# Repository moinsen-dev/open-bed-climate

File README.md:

# Open Bed Climate

**An open-source, local-first bed climate system you can build, repair and adapt yourself.**

Open Bed Climate cools and warms each side of your bed with water, tracks presence, heart rate and breathing,
and runs your sleep temperature schedule — like the commercial "smart mattress cover" systems, but:

- 🔓 **Open:** hardware (CERN-OHL-S-2.0) and software (Apache-2.0), designed clean-room from public information
- 🏠 **Local-first:** no cloud, no account, no subscription; native **Home Assistant** integration
- 🔧 **Standard parts:** PC-watercooling components, Peltier modules, Raspberry Pi Pico, ESP32, certified plug-in power supplies
- 🧩 **DIY kits you can adapt:** one zone or two, cheap or high-performance, three sensing options

> ⚠️ **Safety first.** This project combines water, several hundred watts and a sleeping person.
> Read [SAFETY.md](SAFETY.md) before you build anything. Nothing here is certified.

## Status: design phase. Help us build the first prototype!

| Area | State |
|---|---|
| Feature parity analysis | ✅ [docs/FEATURES.md](docs/FEATURES.md) |
| System design, safety concept | ✅ [docs/design/](docs/design/) · [SAFETY.md](SAFETY.md) |
| Kits and parts catalog | ✅ first version: [hardware/](hardware/) |
| Reference software (thermal model, control + safety logic, protocol, schedules) | ✅ tested: [software/obc](software/obc) |
| Control firmware for the Pico 2 (Rust/embassy) | ✅ compiles, matches the reference; 🔜 first hardware bring-up: [firmware/](firmware/) |
| Hub: ESPHome component + Home Assistant entities, night programs on the hub | ✅ compiles for ESP32-S3, protocol and schedule host-tested; 🔜 first hardware run: [hub/esphome/](hub/esphome/) |
| First physical build + measurements | 🔜 **help wanted, the most valuable contribution right now**: follow the [build guide](docs/build/) |

## Pick a kit

| Kit | Zones | Best for | Approx. coldest water* |
|---|---|---|---|
| [Solo Starter](hardware/kits/solo-starter.toml) | 1 | first build, single sleeper, lowest cost | ~21.7 °C |
| [Duo Standard](hardware/kits/duo-standard.toml) | 2 | couples, strongest cooling from standard parts | ~18.8 °C |
| [Duo Reference](hardware/kits/duo-reference.toml) | 2 | experienced builders, custom PCBs, best biometrics | ~18.5 °C |

\* Model estimate, sleeper in bed in a 25 °C room. All kits warm to 43 °C. Kits are plain TOML files: copy one,
change it, and the test suite checks whether your build can deliver what it claims.

## How it works

```
 bed:   [ water mat ] ←─ water lines ─→ ┌──────────────── hub ────────────────┐
        [ sensing   ] ── data cable ──→ │ Peltier thermal module(s), pump      │
                                        │ Pico 2 control MCU (safety limits)   │
                                        │ ESP32/ESPHome hub ⇄ Home Assistant   │
                                        │ certified 24 V + 12 V supplies       │
                                        └──────────────────────────────────────┘
```

Details: [architecture](docs/design/00-architecture.md) · [thermal](docs/design/01-thermal-fluidics.md) ·
[electrical safety](docs/design/02-electrical-safety.md) · [sensing](docs/design/03-sensing-biometrics.md) ·
[protocol](docs/design/04-firmware-protocol.md) · [software](docs/design/05-bed-software.md) ·
[open decisions](docs/design/OPEN-DECISIONS.md)

## Get involved

Builders, parts hunters, electronics and textile people, firmware and Home Assistant developers, writers:
there is a place for you. Start with [CONTRIBUTING.md](CONTRIBUTING.md).

**Build it:** the [build guide for prototype 0](docs/build/) (Solo Starter, bench first, then bed) takes you
step by step from parts to a commissioned unit and the measurements the model still needs.

```sh
cd software/obc && uv run pytest -q    # reference model, safety logic, kit checks
cd firmware && cargo test               # firmware core vs. golden vectors
```

## Background

Commercial systems in this space (e.g. Eight Sleep Pod) are cloud-bound and subscription-based. A community has
already built local replacements for older Pod hardware; see [docs/research/prior-art.md](docs/research/prior-art.md).
Open Bed Climate takes a different route: **our own open hardware**, so nobody depends on a vendor's servers to sleep well.
Open Bed Climate is not affiliated with or endorsed by Eight Sleep.

## License
Software and documentation: [Apache-2.0](LICENSE) · Hardware designs: [CERN-OHL-S-2.0](LICENSE-HARDWARE)

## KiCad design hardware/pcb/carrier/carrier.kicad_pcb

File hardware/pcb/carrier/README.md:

# Tier 0 carrier PCB, Rev A

> ⚠️ **Rev A is UNTESTED: review it before you order.** Nobody has built or measured it yet. Read
> [SAFETY.md](../../../SAFETY.md) first. Please post a build report if you build one.

The carrier replaces the perfboard and loose breakout boards of [step 2](../../../docs/build/02-control-board.md)
with one 100 × 100 mm, 2-layer board, so a small series (~10 units) can be ordered assembled. It carries **signals
and the 12 V aux rail only**. The TEC high-current path stays off-board, wired with ≥ 2.5 mm²:
24 V brick → DPS5020 → 20 A fuse → zone relay → polarity relays → TECs
([step 3](../../../docs/build/03-power-path.md)).

What plugs in:
- Raspberry Pi Pico 2 on 2 × 1x20 female headers
- ESP32-S3-DevKitC-1 on 2 × 1x22 female headers
- Screw terminals for every external wire: 5.08 mm for 12 V loads and power, 3.5 mm for sensors

Licence: CERN-OHL-S-2.0, like the rest of the hardware.

## Block diagram

```mermaid
flowchart LR
  IN["12 V aux brick<br/>barrel jack (Solo, <= 5 A) or 12V IN screw terminal"] --> F["mini blade fuse<br/>5 A (7.5 A on 2 oz)"] --> TVS["SMBJ15A TVS"] --> RP["P-FET reverse-polarity<br/>(AOD4185)"] --> V12(("+12V"))
  V12 --> BUCK["LM2596S-5.0<br/>12 -> 5 V, 3 A"] --> V5(("+5V"))
  V5 -- "SS34" --> PICO["Pico 2 (VSYS)"]
  V5 -- "SS34" --> ESP["ESP32-S3-DevKitC-1 (5V)"]
  PICO -- "3V3 OUT" --> V33(("+3V3"))
  PICO <-- "OPL UART GP0/GP1 460800 Bd" --> ESP
  ESP --- I2CH["I2C HUB header<br/>(room SHT45)"]
  PICO -- "I2C0 GP8/GP9" --> ADS["ADS1115 @0x48"] --- NTC["4x NTC divider<br/>10k 0.1 % + RC"]
  PICO -- "UART1 GP4/GP5, DE GP6" --> RS["SP3485"] --> DPS["RS-485 A/B/GND<br/>to the DPS module(s)"]
  PICO -- "GP10..13 / GP16..19" --> DRV["8x AO3400A low-side<br/>220R gate, 4.7k pull-down, SS34 flyback"]
  V12 --> LOOP["CUTOFF LOOP terminal<br/>(bimetal cutoffs in series)"] --> COIL["zone relay coil"] --> DRV
  V12 --> LOADS["polarity coils A/B, pump, fan"] --> DRV
  FLOW["flow GP14/GP20"] & LEAK["leak GP21"] & LEVEL["level GP22"] -- "1k + BAT54S clamp + 10k pull-up" --> PICO
```

## Terminals and pins (cross-referenced to `board.rs`)

The pin map comes from [`firmware/obc-pico2/src/board.rs`](../../../firmware/obc-pico2/src/board.rs).
[`software/obc/tests/test_carrier_pcb.py`](../../../software/obc/tests/test_carrier_pcb.py) parses
`carrier.kicad_pcb` and checks it against `board.rs` and
[`hub/esphome/obc-hub-common.yaml`](../../../hub/esphome/obc-hub-common.yaml) in CI. Pin 1 is the square pad.
Zone 0's terminals run along the top edge, zone 1's along the bottom edge (mirrored). Silk labels sit next to each
block, with the pin names written in left-to-right order.

| Terminal (zone 0 / zone 1) | Pins | Function | Pico 2 (`board.rs`) |
|---|---|---|---|
| J13 / J20 `CUTOFF LOOP` | 1 `12V` out, 2 `RET` | +12 V out to the bimetal cutoffs in series (all 50 °C and 80 °C) and back. **The return is the only feed of the zone relay coil.** | none, pure hardware |
| J14 / J21 `ZONE RLY` | 1 `+` coil (from RET), 2 `−` driver | zone (enable) relay coil, flyback across the coil | GP10 / GP16 |
| J15 + J16 / J22 + J23 `POL A`, `POL B` | 1 `+` 12 V, 2 `−` driver | polarity relay coils: 2 × SPDT (shopping list) on A and B, both switched by one MOSFET, each with its own flyback. **One DPDT relay: use POL A only.** | GP11 / GP17 (low = cool) |
| J17 / J24 `PUMP` | 1 `+` 12 V, 2 `−` | pump, ≥ 2 A, PWM-capable MOSFET | GP12 / GP18 |
| J18 / J25 `FAN` | 1 `+` 12 V, 2 `−` | heatsink fans, ≥ 2 A | GP13 / GP19 |
| J19 / J26 `FLOW` | 1 `5V`, 2 `G`, 3 `S` | hall flow sensor; 1 kΩ series, BAT54S clamp to 3.3 V/GND, 10 kΩ pull-up (5 V outputs are safe) | GP14 / GP20 |
| J4 / J6 `NTC WTR` | 1 `N` node, 2 `G` | water NTC: 3.3 V → 10 kΩ 0.1 % → node → NTC → GND, 1 kΩ/100 nF to the ADS | ADS1115 A0 / A2 |
| J5 / J7 `NTC HOT` | 1 `N`, 2 `G` | TEC hot-side NTC | ADS1115 A1 / A3 |

| Terminal (right edge) | Pins | Function | Pico 2 |
|---|---|---|---|
| J10 `RS-485` | 1 `A`, 2 `B`, 3 `G` | Modbus to the DPS module(s); JP1 `TERM` = 120 Ω across A/B (fit only if this end has no other termination) | UART1 GP4 (TX→DI) / GP5 (RO→RX), DE + /RE on GP6 (10 kΩ pull-down = receive) |
| J11 `LEAK` | 1 `12V`, 2 `G`, 3 `S` | leak module (powered from 12 V); contact to GND while dry. LOW = dry, open = fault | GP21 (10 kΩ pull-up) |
| J12 `LEVEL` | 1 `5V`, 2 `G`, 3 `S` | level sensor at 5 V; LOW = OK, open = fault. The clamp makes a 5 V output safe; the divider from the shopping list is not needed | GP22 (10 kΩ pull-up) |
| J2 `12V IN` | 1 `+12V`, 2 `GND` | 12 V aux brick (use this one for Duo) | |
| J1 barrel 5.5 × 2.5 | centre + | in parallel with J2. **Solo only, ≤ 5 A** | |
| J3 `STAR GND` | 1, 2 GND | **one** wire to the star point near the DPS (24 V −). Do not link 12 V − and 24 V − anywhere else | |

| Header | Pins | Notes |
|---|---|---|
| J9 `I2C HUB` | 1 ESP 3V3, 2 GND, 3 SDA = ESP32 GPIO8, 4 SCL = GPIO9 | room SHT45 for the dew-point guard. 4.7 kΩ pull-ups on board. The hub YAML only mentions the SHT45 in a comment; add `i2c: {sda: GPIO8, scl: GPIO9}` and an `sht4x` sensor, then set `room_temperature` / `room_humidity` |
| J8 `I2C PICO` | 1 3V3, 2 GND, 3 SDA = GP8, 4 SCL = GP9 | expansion on the ADS1115 bus (avoid address 0x48) |
| TP1–TP4 | 12V, 5V, 3V3, GND | test points (2 mm pads) |

All eight driver gates have a **4.7 kΩ pull-down** (RP2350-E9: ≤ 8.2 kΩ). An unflashed, crashed or reset Pico
leaves every output off, and the test checks every gate for it. Each zone relay coil gets +12 V **only** through its
CUTOFF LOOP terminal. An open cutoff or an unplugged loop drops the relay whatever the MCU does, and the test checks
that too. The flyback diode sits directly across the coil, so an opening bimetal never has to break the coil
current as an arc.

## Files

| Path | What |
|---|---|
| `scripts/design.py` | **source of truth**: every part with symbol, footprint, value, LCSC number and the net on each pin |
| `scripts/gen_lib.py` | project library: ESP32-S3-DevKitC-1 symbol, socket footprints for both modules |
| `scripts/gen_sch.py` | `carrier.kicad_sch`: one sheet, grouped by function, net labels on every pin, no-connect flags, power flags |
| `scripts/gen_pcb.py` | `carrier.kicad_pcb`: placement, nets, outline, silkscreen, net classes, JLC rules (`carrier.kicad_pro`) |
| `scripts/route.py` | Freerouting autoroute, GND pours on both layers, GND stitching vias |
| `scripts/silk.py` | post-route silkscreen pass: connector refs to F.Fab, test point / header / jumper labels, back-side labels for the NTC terminals hidden by the barrel jack |
| `scripts/fab.py` | ERC/DRC, Gerbers + drill, JLC BOM/CPL, full BOM, PDFs, renders into `fab/` |
| `build.sh` | runs all of the above |
| `fab/` | `carrier-rev-a-gerbers.zip`, `jlc-bom.csv`, `jlc-cpl.csv`, `bom-full.csv`, `carrier-schematic.pdf`, `carrier-assembly-top.pdf`, `carrier.net`, `reports/` (ERC, DRC), `renders/` |

Rebuild (KiCad 10, and Freerouting 1.9.0 on Java 17: `freerouting-1.9.0.jar` from
<https://github.com/freerouting/freerouting/releases/tag/v1.9.0>):

```sh
FREEROUTING_JAR=~/Downloads/freerouting-1.9.0.jar JAVA=/opt/homebrew/opt/openjdk@17/bin/java ./build.sh
```

Change the design in `scripts/design.py`, never in the generated KiCad files. Freerouting isn't deterministic, so a
rebuild gives different traces; re-run DRC and look at the renders.

## Board

- **100 × 100 mm, 2 layers**, 1.6 mm, M3 mounting holes (4, at the free spots, not the corners: the terminal rows
  run the full width). 126 footprints: 88 SMD parts for JLC assembly, the rest are THT/hand-soldered or holes.
- Track widths: signals 0.25 mm, loads (drains, coils, 5 V) 0.8 mm, 12 V 1.5 mm. GND pours on both layers, about
  200 vias including GND stitching. JLC-safe rules: clearance 0.2 mm (MSOP pads trimmed to TI's 0.30 mm land
  pattern), vias 0.6/0.3 mm, hole to hole ≥ 0.5 mm, copper to edge ≥ 0.3 mm. No copper under the ESP32 antenna.
- **Checks (Rev A as generated): ERC 0 violations. DRC 0 errors, 0 unconnected, schematic parity clean.**
  15 silkscreen-only warnings (small labels touching a pad or another label) are left; JLC clips silk on pads.
  Pin labels next to the terminals are 0.8 mm high: check they're legible in JLC's preview.
  Reports: `fab/reports/`.
- Renders: `fab/renders/render-top.png`, `render-bottom.png`, `render-3d.png`, `top-layers.svg`,
  `bottom-layers.svg`. The 12 × 12 mm inductor has no 3D model in KiCad's library and shows as a bare footprint.

## Ordering (JLCPCB)

1. **PCB**: upload `fab/carrier-rev-a-gerbers.zip`, 2 layers, 100 × 100 mm, 1.6 mm FR-4, HASL lead-free, 1 oz
   copper (5 A input). For Duo boards with all 12 V loads near their maximum, choose 2 oz outer copper (7.5 A, see
   limitations). Quantity 10.
2. **Assembly**: PCBA, Economic, top side, "Confirm parts placement". Upload `fab/jlc-bom.csv` and `fab/jlc-cpl.csv`.
3. In the BOM step, check every match. Parts **without an LCSC number** need one picked from JLC's library first:
   - AOD4185 (P-FET, TO-252, −40 V, ≤ 15 mΩ)
   - SS54 (5 A Schottky, SMC)
   - BZT52C12 (SOD-123)
   - 33 µH ≥ 4 A shielded 12 × 12 mm inductor
   - 100 µF 35 V and 220 µF 16 V electrolytics (6.3 × 7.7 mm, low ESR)
   - 10 kΩ **0.1 %** 0603 resistors (×4, NTC dividers: these set the temperature accuracy)

   The numbers marked "check" in `bom-full.csv` are the usual JLC basic parts but weren't confirmed on a product
   page while Rev A was drawn up.
4. In the placement preview, **check the rotation of every polarized part**: diodes, LED, electrolytics, SOT-23,
   ADS1115, SP3485, LM2596. KiCad and JLC rotation conventions differ for some packages; fix any wrong one in the
   preview.
5. **Hand-soldered THT parts** (not in the JLC files; buy them separately or add them as JLC THT assembly):

   | Qty | Part |
   |---|---|
   | 14 | screw terminal 5.08 mm, 2-pin (Phoenix MKDS 1,5/2-5.08 or compatible, e.g. KF128/DG128-2P) |
   | 4 | screw terminal 3.5 mm, 2-pin (NTC) |
   | 5 | screw terminal 3.5 mm, 3-pin (flow ×2, RS-485, leak, level) |
   | 2 + 2 | 1x20 and 1x22 female headers, 2.54 mm (Pico 2 / ESP32 sockets) |
   | 1 | DC barrel jack 5.5 × 2.5 mm, 3-pin THT, horizontal, with the pin layout of KiCad's `BarrelJack_Horizontal` (e.g. CUI PJ-063AH-class): **check the pins against the footprint**, a mismatched jack leaves GND or +12 V open |
   | 1 | Keystone 3568 mini blade fuse holder + ATM fuse: 5 A (1 oz board) or 7.5 A (2 oz board) |
   | 2 + 1 | 1x4 and 1x2 pin headers, jumper |
   | 4 | test points (2 mm pads): bare wire loops or nothing |

   Check each terminal block's footprint against your part. The Phoenix footprints assume the wire entry faces the
   board edge (verify on the 3D render before ordering).

### Cost estimate, 10 assembled boards (Oct 2026, rough)

| Item | ~USD for 10 |
|---|---|
| PCB 2 layers 100 × 100 mm, 1 oz | 5–10 (2 oz: +15) |
| PCBA setup + stencil | 10 |
| Extended-part fees (~10 unique extended parts × $3) | 30 |
| SMD components (ADS1115 ≈ $3 is the biggest item) | 60–80 |
| Placement and soldering | 5–10 |
| THT parts (≈25 terminals, sockets, jack, fuse holder) | 60–90 |
| Shipping to the EU + import VAT | 40–60 |
| **Total** | **≈ 210–290, i.e. ≈ €20–27 per board** |

That's without the Pico 2 and ESP32-S3-DevKitC-1 (about €6 + €15 each). Prices move: get a live quote.
AISLER (EU, PCB + assembly) or PCBWay take the same Gerbers. Their BOM formats differ: use `bom-full.csv` and
the KiCad position file `fab/reports/pos-kicad.csv`.

## Known limitations (Rev A)

- **Untested.** Not built, not powered, not measured. The first boards are a bring-up exercise: follow the
  [step 2 checkpoint](../../../docs/build/02-control-board.md) (gate pull-downs, reset test, rails) before you
  connect relays or TECs.
- **12 V current.** The 12 V traces are 1.5 mm (IPC-2221, external layer): about 4.5 A at +20 °C on 1 oz copper,
  about 7.5 A on 2 oz. Each zone's branch carries at most ~3.5 A (pump + fans + coils), but the input path carries
  the total. So: **1 oz board → 5 A fuse, ≤ 5 A total** (enough for Solo, ~3–4 A). **Duo near full load → order
  2 oz copper and fit a 7.5 A fuse.** Measure the real 12 V current at bring-up either way. The barrel jack is for
  ≤ 5 A only.
- **Reverse protection** drops ~0.1 V at 7 A (AOD4185, ~0.7 W). A 24 V brick plugged in by mistake makes the
  SMBJ15A TVS conduct and blows the fuse. It's a crowbar, so check the fuse after any wrong plug.
- **5 V back-feed.** The board's 5 V reaches the Pico and the ESP32 through Schottkys, so USB on either module
  never back-feeds into the board. Whether the DevKitC's own USB port can be back-fed from its 5V pin depends on
  the DevKitC revision. Prefer **not** to plug ESP32 USB in while the board is powered.
- **ESP32 row spacing** (22.86 mm) and pin order come from Espressif's DevKitC-1 v1.1 dimension drawing (DXF) and
  user guide. v1.0 boards have the same header. **Measure your module with calipers** before ordering. A clone with
  25.4 mm rows won't fit.
- **ESP32 antenna**: the antenna end has no copper on either layer, but the module still sits over the carrier's
  ground plane. Mount the carrier so the antenna isn't covered by metal.
- **Under-module parts**: low SMD parts sit between the socket rows of both modules. They are 8.5 mm below the
  module. Unplug the module to probe them.
- **Freerouting**: the traces are autorouted, not hand-optimised. Before ordering, look at the buck loop
  (LM2596 → SS54 → inductor → output cap) and the 12 V path in KiCad, and shorten them by hand if you can.
- **Pump/fan PWM**: since firmware 0.2 the MOSFETs switch the pump and fan supply at 25 kHz PWM. Use 2- or 3-pin
  fans; 4-wire PWM fans and the DDC's PWM input aren't broken out.
- **No on-board RS-485 bias resistors and no TVS on A/B.** The DPS-side adapter usually biases the bus. Keep the
  bus short and inside the enclosure.
- **LCSC numbers**: about half were confirmed on a product page (marked in `bom-full.csv`). The rest need checking
  in JLC's BOM matcher, and a few must be picked (see Ordering).

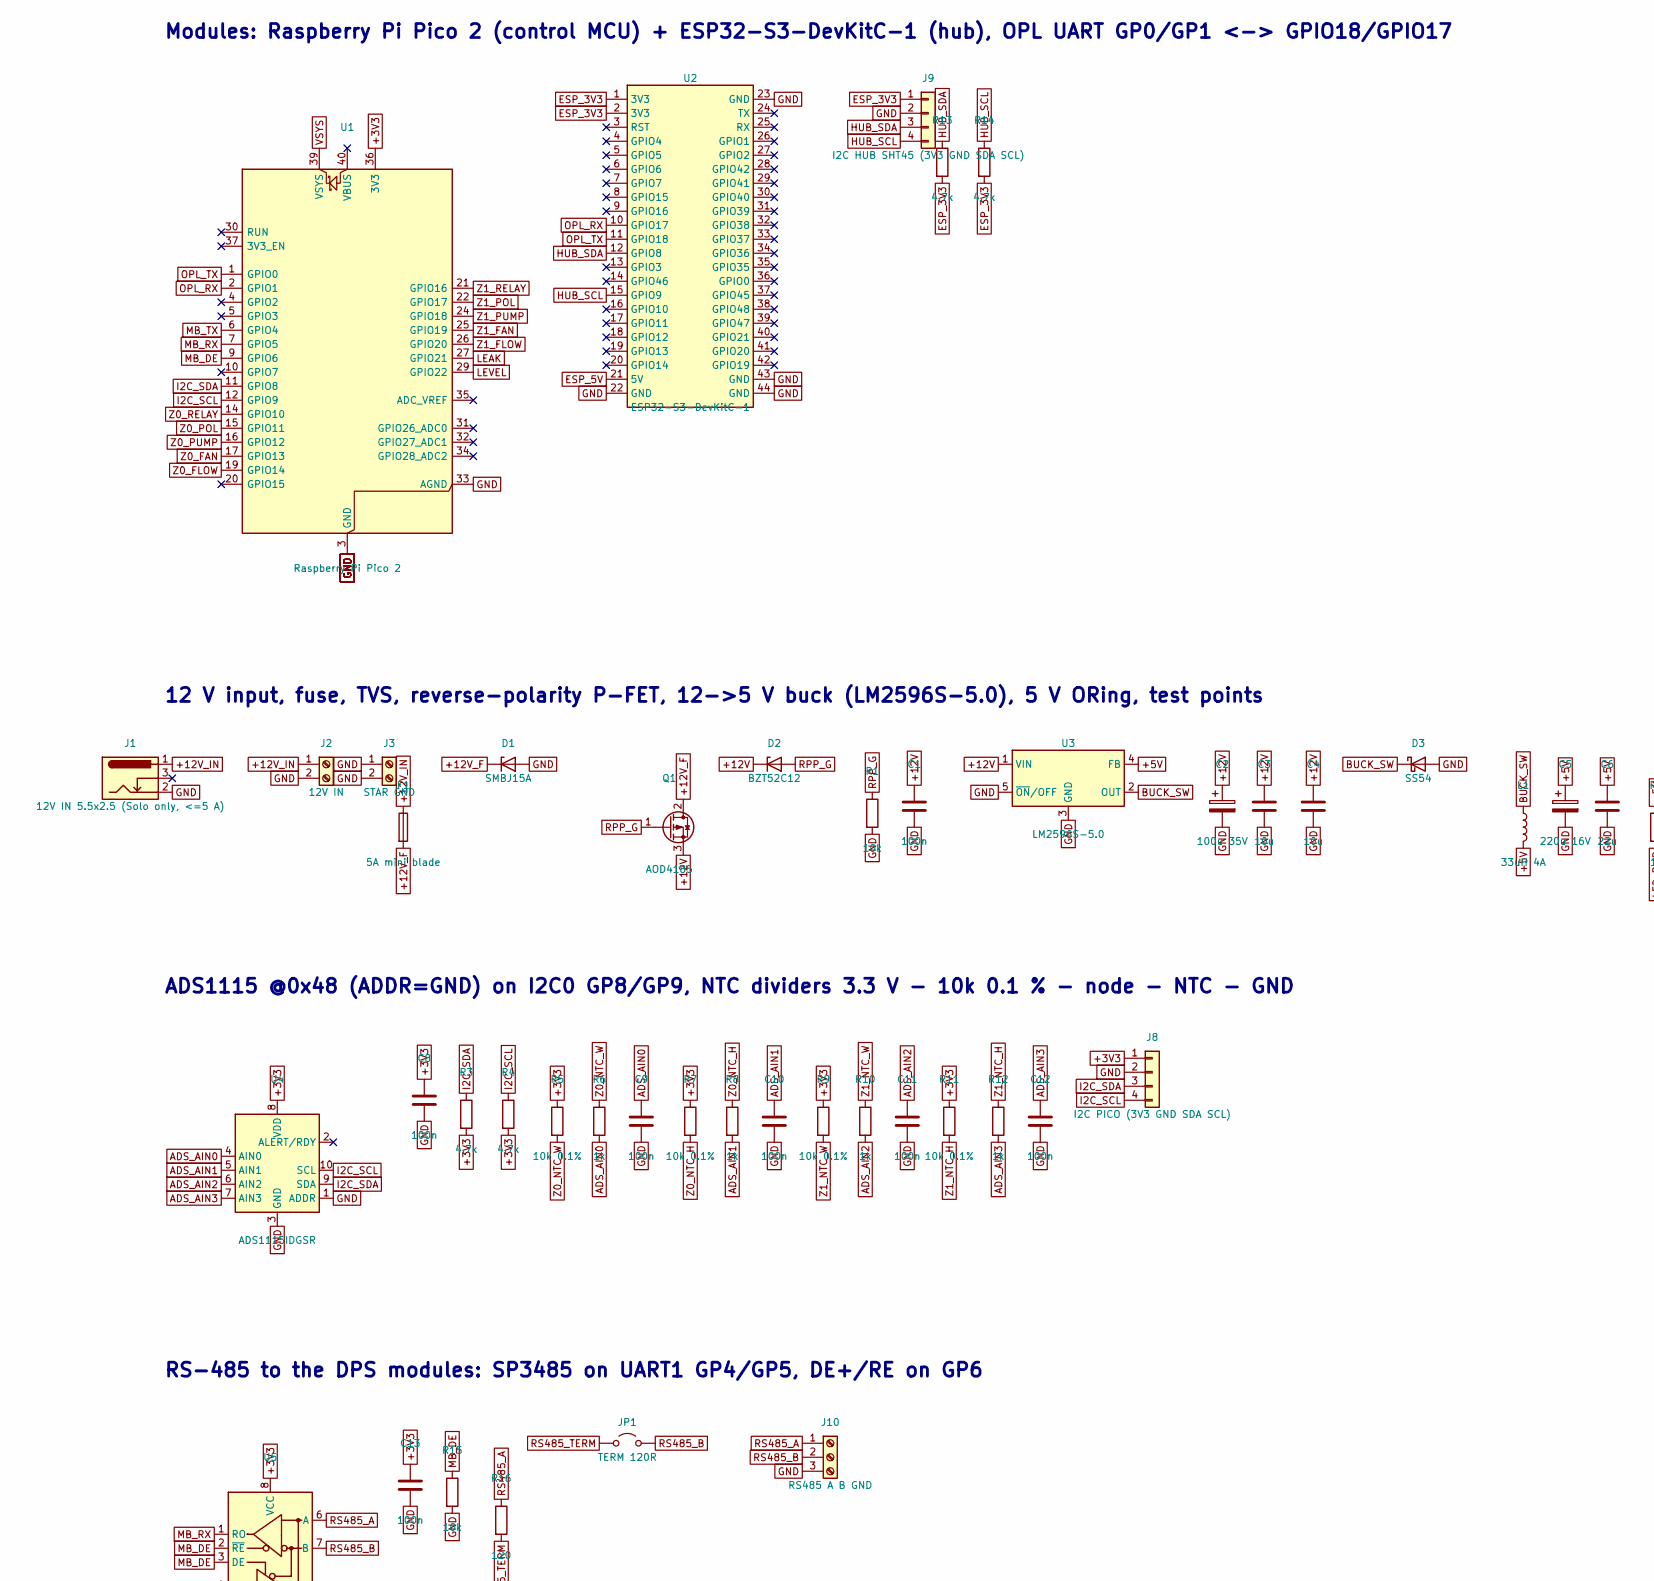
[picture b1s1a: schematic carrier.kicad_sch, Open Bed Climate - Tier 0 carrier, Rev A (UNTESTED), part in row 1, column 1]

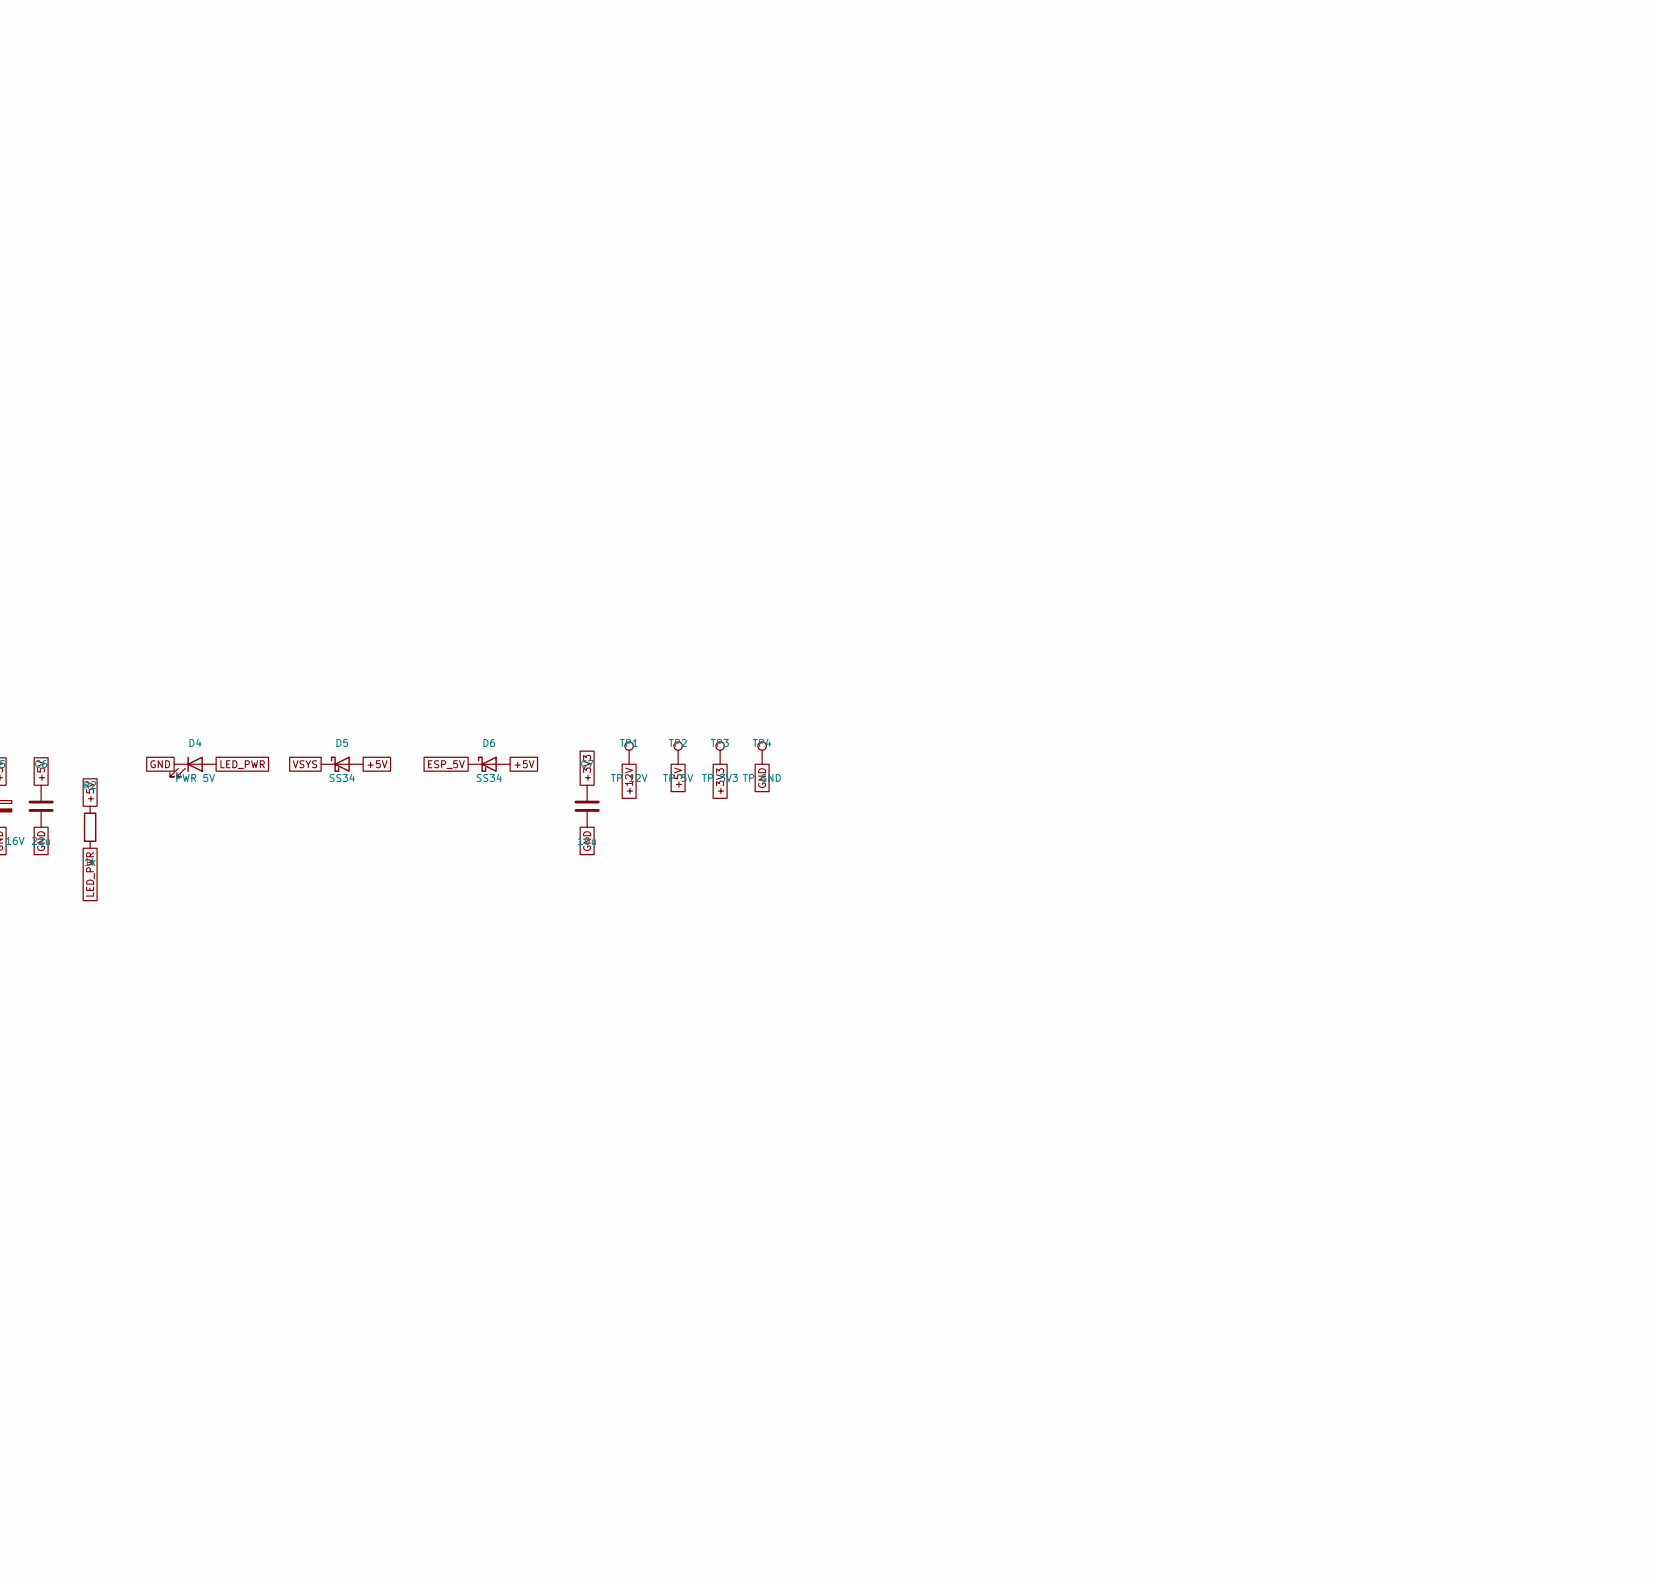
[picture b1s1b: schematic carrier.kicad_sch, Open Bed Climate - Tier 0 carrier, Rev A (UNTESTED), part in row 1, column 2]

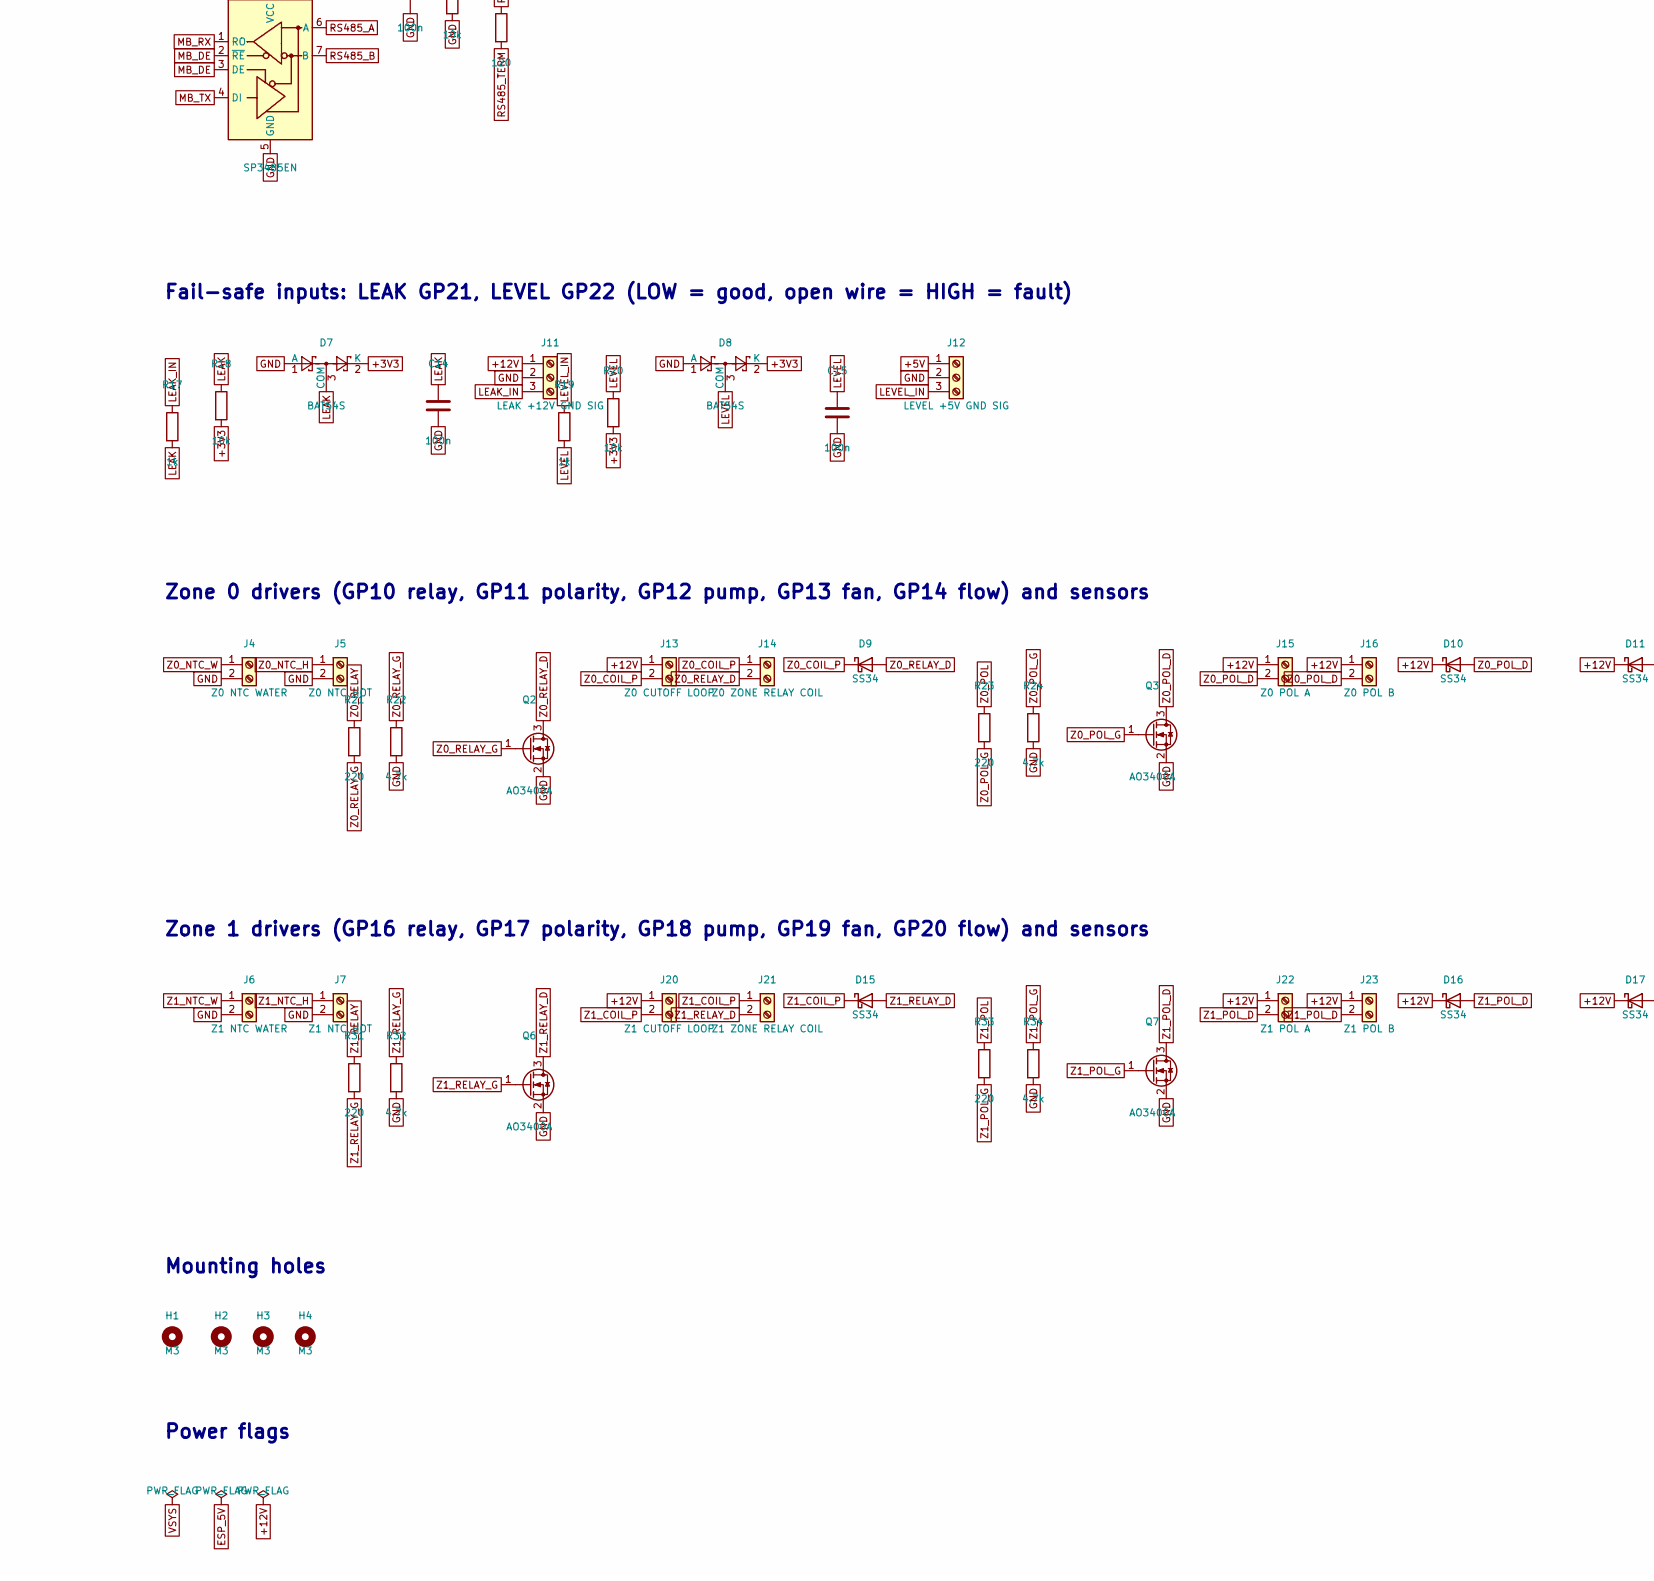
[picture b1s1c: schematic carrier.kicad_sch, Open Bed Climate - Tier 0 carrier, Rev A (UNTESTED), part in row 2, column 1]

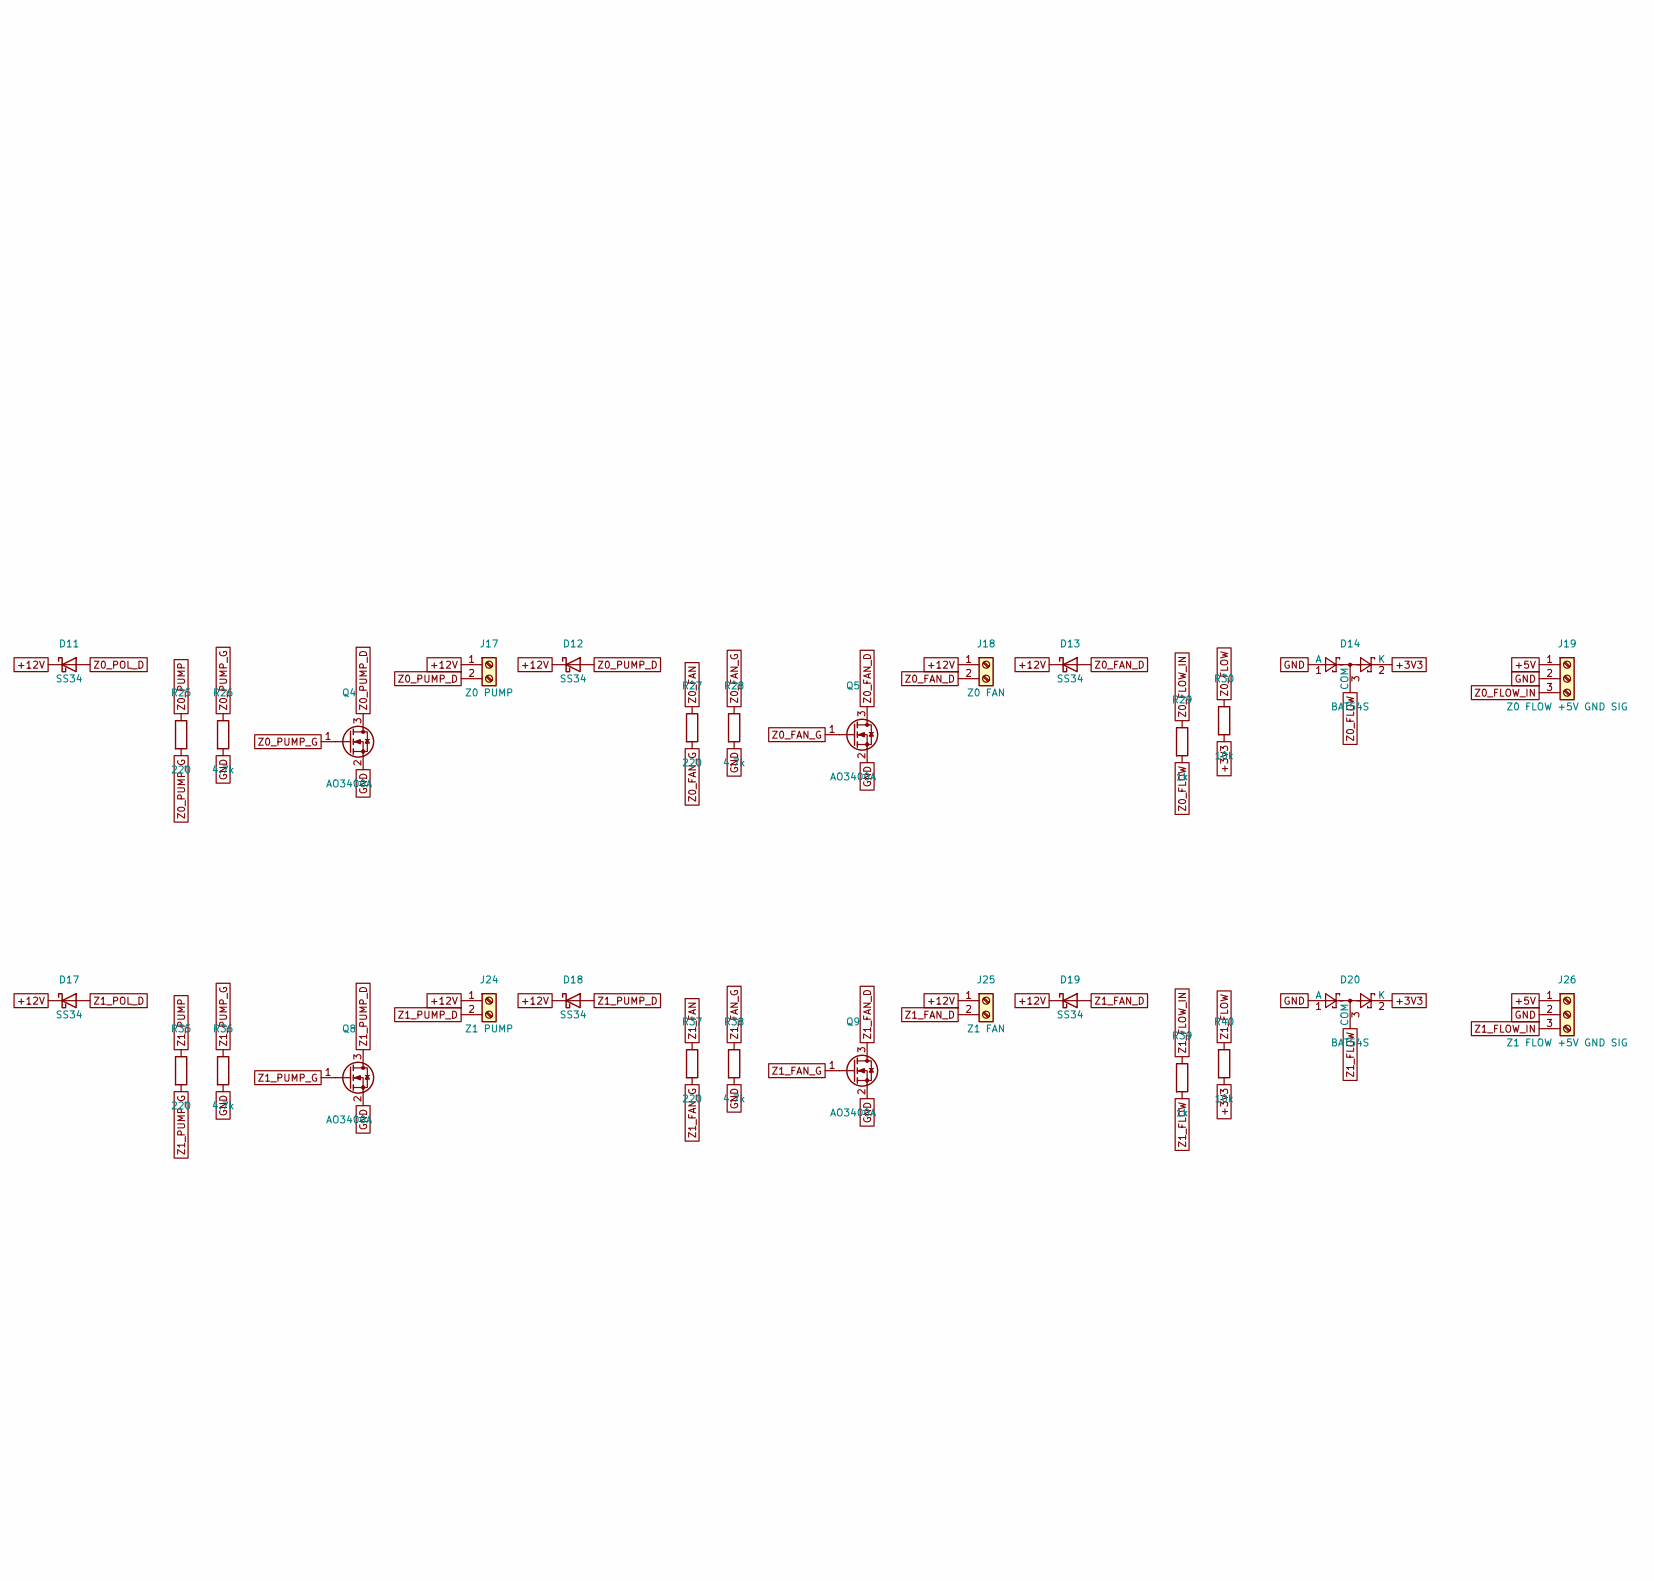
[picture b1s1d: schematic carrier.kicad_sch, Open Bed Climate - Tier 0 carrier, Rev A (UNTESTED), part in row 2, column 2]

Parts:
C1, C8, C9, C10, C11, C12, C13, C14, C15: 100n; C_0603_1608Metric; LCSC C14663
C2: 100u 35V; CP_Elec_6.3x7.7
C3, C4, C7: 10u; C_0805_2012Metric; LCSC C15850
C5: 220u 16V; CP_Elec_6.3x7.7
C6: 22u; C_0805_2012Metric; LCSC C45783
D1: SMBJ15A; D_SMB; LCSC C699013
D2: BZT52C12; D_SOD-123
D3: SS54; D_SMC
D4: PWR 5V; LED_0603_1608Metric; LCSC C2286
D5, D6, D9, D10, D11, D12, D13, D15, D16, D17, D18, D19: SS34; D_SMA; LCSC C8678
D7, D8, D14, D20: BAT54S; SOT-23; LCSC C916425
F1: 5A mini blade; Fuseholder_Blade_Mini_Keystone_3568
H1, H2, H3, H4: M3; MountingHole_3.2mm_M3
J1: 12V IN 5.5x2.5 (Solo only, <=5 A); BarrelJack_Horizontal
J2: 12V IN; TerminalBlock_Phoenix_MKDS-1,5-2-5.08_1x02_P5.08mm_Horizont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
J3: STAR GND; TerminalBlock_Phoenix_MKDS-1,5-2-5.08_1x02_P5.08mm_Horizont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
J4: Z0 NTC WATER; TerminalBlock_Phoenix_PT-1,5-2-3.5-H_1x02_P3.50mm_Horizontal
J5: Z0 NTC HOT; TerminalBlock_Phoenix_PT-1,5-2-3.5-H_1x02_P3.50mm_Horizontal
J6: Z1 NTC WATER; TerminalBlock_Phoenix_PT-1,5-2-3.5-H_1x02_P3.50mm_Horizontal
J7: Z1 NTC HOT; TerminalBlock_Phoenix_PT-1,5-2-3.5-H_1x02_P3.50mm_Horizontal
J8: I2C PICO (3V3 GND SDA SCL); PinHeader_1x04_P2.54mm_Vertical
J9: I2C HUB SHT45 (3V3 GND SDA SCL); PinHeader_1x04_P2.54mm_Vertical
J10: RS485 A B GND; TerminalBlock_Phoenix_PT-1,5-3-3.5-H_1x03_P3.50mm_Horizontal
J11: LEAK +12V GND SIG; TerminalBlock_Phoenix_PT-1,5-3-3.5-H_1x03_P3.50mm_Horizontal
J12: LEVEL +5V GND SIG; TerminalBlock_Phoenix_PT-1,5-3-3.5-H_1x03_P3.50mm_Horizontal
J13: Z0 CUTOFF LOOP; TerminalBlock_Phoenix_MKDS-1,5-2-5.08_1x02_P5.08mm_Horizont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
J14: Z0 ZONE RELAY COIL; TerminalBlock_Phoenix_MKDS-1,5-2-5.08_1x02_P5.08mm_Horizont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
J15: Z0 POL A; TerminalBlock_Phoenix_MKDS-1,5-2-5.08_1x02_P5.08mm_Horizont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
J16: Z0 POL B; TerminalBlock_Phoenix_MKDS-1,5-2-5.08_1x02_P5.08mm_Horizont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
J17: Z0 PUMP; TerminalBlock_Phoenix_MKDS-1,5-2-5.08_1x02_P5.08mm_Horizont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
J18: Z0 FAN; TerminalBlock_Phoenix_MKDS-1,5-2-5.08_1x02_P5.08mm_Horizont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
J19: Z0 FLOW +5V GND SIG; TerminalBlock_Phoenix_PT-1,5-3-3.5-H_1x03_P3.50mm_Horizontal
J20: Z1 CUTOFF LOOP; TerminalBlock_Phoenix_MKDS-1,5-2-5.08_1x02_P5.08mm_Horizont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
J21: Z1 ZONE RELAY COIL; TerminalBlock_Phoenix_MKDS-1,5-2-5.08_1x02_P5.08mm_Horizont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
J22: Z1 POL A; TerminalBlock_Phoenix_MKDS-1,5-2-5.08_1x02_P5.08mm_Horizont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
J23: Z1 POL B; TerminalBlock_Phoenix_MKDS-1,5-2-5.08_1x02_P5.08mm_Horizont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
J24: Z1 PUMP; TerminalBlock_Phoenix_MKDS-1,5-2-5.08_1x02_P5.08mm_Horizont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
J25: Z1 FAN; TerminalBlock_Phoenix_MKDS-1,5-2-5.08_1x02_P5.08mm_Horizont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
J26: Z1 FLOW +5V GND SIG; TerminalBlock_Phoenix_PT-1,5-3-3.5-H_1x03_P3.50mm_Horizontal
JP1: TERM 120R; PinHeader_1x02_P2.54mm_Vertical
L1: 33uH 4A; L_12x12mm_H8mm
Q1: AOD4185; TO-252-2
Q2, Q3, Q4, Q5, Q6, Q7, Q8, Q9: AO3400A; SOT-23; LCSC C20917
R1, R15, R18, R20, R30, R40: 10k; R_0603_1608Metric; LCSC C25804
R2, R6, R8, R10, R12, R17, R19, R29, R39: 1k; R_0603_1608Metric; LCSC C21190
R3, R4, R13, R14, R22, R24, R26, R28, R32, R34, R36, R38: 4.7k; R_0603_1608Metric; LCSC C23162
R5, R7, R9, R11: 10k 0.1%; R_0603_1608Metric
R16: 120; R_0603_1608Metric; LCSC C22787
R21, R23, R25, R27, R31, R33, R35, R37: 220; R_0603_1608Metric; LCSC C22962
TP1: TP 12V; TestPoint_THTPad_D2.0mm_Drill1.0mm
TP2: TP 5V; TestPoint_THTPad_D2.0mm_Drill1.0mm
TP3: TP 3V3; TestPoint_THTPad_D2.0mm_Drill1.0mm
TP4: TP GND; TestPoint_THTPad_D2.0mm_Drill1.0mm
U1: Raspberry Pi Pico 2; RaspberryPi_Pico2_Socket
U2: ESP32-S3-DevKitC-1; ESP32-S3-DevKitC-1_Socket
U3: LM2596S-5.0; TO-263-5_TabPin3; LCSC C116713
U4: ADS1115IDGSR; MSOP-10_3x3mm_P0.5mm; LCSC C37593
U5: SP3485EN; SOIC-8_3.9x4.9mm_P1.27mm; LCSC C8963

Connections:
+3V3: C7.1, C8.1, C13.1, D7.2 (K), D8.2 (K), D14.2 (K), D20.2 (K), J8.1, R3.2, R4.2, R5.1, R7.1, R9.1, R11.1, R18.2, R20.2, R30.2, R40.2, TP3.1, U1.36 (3V3), U4.8 (VDD), U5.8 (VCC)
+5V: C5.1, C6.1, D5.2 (A), D6.2 (A), J12.1, J19.1, J26.1, L1.2, R2.1, TP2.1, U3.4 (FB)
+12V: C1.1, C2.1, C3.1, C4.1, D2.1 (K), D10.1 (K), D11.1 (K), D12.1 (K), D13.1 (K), D16.1 (K), D17.1 (K), D18.1 (K), D19.1 (K), J11.1, J13.1, J15.1, J16.1, J17.1, J18.1, J20.1, J22.1, J23.1, J24.1, J25.1, Q1.3 (S), TP1.1, U3.1 (VIN)
+12V_F: D1.1 (K), F1.2, Q1.2 (D)
+12V_IN: F1.1, J1.1, J2.1
ADS_AIN0: C9.1, R6.2, U4.4 (AIN0)
ADS_AIN1: C10.1, R8.2, U4.5 (AIN1)
ADS_AIN2: C11.1, R10.2, U4.6 (AIN2)
ADS_AIN3: C12.1, R12.2, U4.7 (AIN3)
BUCK_SW: D3.1 (K), L1.1, U3.2 (OUT)
ESP_3V3: J9.1, R13.2, R14.2, U2.1 (3V3), U2.2 (3V3)
ESP_5V: D6.1 (K), U2.21 (5V)
GND: C1.2, C2.2, C3.2, C4.2, C5.2, C6.2, C7.2, C8.2, C9.2, C10.2, C11.2, C12.2, C13.2, C14.2, C15.2, D1.2 (A), D3.2 (A), D4.1 (K), D7.1 (A), D8.1 (A), D14.1 (A), D20.1 (A), J1.2, J2.2, J3.1, J3.2, J4.2, J5.2, J6.2, J7.2, J8.2, J9.2, J10.3, J11.2, J12.2, J19.2, J26.2, Q2.2 (S), Q3.2 (S), Q4.2 (S), Q5.2 (S), Q6.2 (S), Q7.2 (S), Q8.2 (S), Q9.2 (S), R1.2, R15.2, R22.2, R24.2, R26.2, R28.2, R32.2, R34.2, R36.2, R38.2, TP4.1, U1.3 (GND), U1.8 (GND), U1.13 (GND), U1.18 (GND), U1.23 (GND), U1.28 (GND), U1.33 (AGND), U1.38 (GND), U2.22 (GND), U2.23 (GND), U2.43 (GND), U2.44 (GND), U3.3 (GND), U3.5 (~ON/OFF), U4.1 (ADDR), U4.3 (GND), U5.5 (GND)
HUB_SCL: J9.4, R14.1, U2.15 (GPIO9)
HUB_SDA: J9.3, R13.1, U2.12 (GPIO8)
I2C_SCL: J8.4, R4.1, U1.12 (GPIO9), U4.10 (SCL)
I2C_SDA: J8.3, R3.1, U1.11 (GPIO8), U4.9 (SDA)
LEAK: C14.1, D7.3 (COM), R17.2, R18.1, U1.27 (GPIO21)
LEAK_IN: J11.3, R17.1
LED_PWR: D4.2 (A), R2.2
LEVEL: C15.1, D8.3 (COM), R19.2, R20.1, U1.29 (GPIO22)
LEVEL_IN: J12.3, R19.1
MB_DE: R15.1, U1.9 (GPIO6), U5.2 (~RE), U5.3 (DE)
MB_RX: U1.7 (GPIO5), U5.1 (RO)
MB_TX: U1.6 (GPIO4), U5.4 (DI)
OPL_RX: U1.2 (GPIO1), U2.10 (GPIO17)
OPL_TX: U1.1 (GPIO0), U2.11 (GPIO18)
RPP_G: D2.2 (A), Q1.1 (G), R1.1
RS485_A: J10.1, R16.1, U5.6 (A)
RS485_B: J10.2, JP1.2 (B), U5.7 (B)
RS485_TERM: JP1.1 (A), R16.2
VSYS: D5.1 (K), U1.39 (VSYS)
Z0_COIL_P: D9.1 (K), J13.2, J14.1
Z0_FAN: R27.1, U1.17 (GPIO13)
Z0_FAN_D: D13.2 (A), J18.2, Q5.3 (D)
Z0_FAN_G: Q5.1 (G), R27.2, R28.1
Z0_FLOW: D14.3 (COM), R29.2, R30.1, U1.19 (GPIO14)
Z0_FLOW_IN: J19.3, R29.1
Z0_NTC_H: J5.1, R7.2, R8.1
Z0_NTC_W: J4.1, R5.2, R6.1
Z0_POL: R23.1, U1.15 (GPIO11)
Z0_POL_D: D10.2 (A), D11.2 (A), J15.2, J16.2, Q3.3 (D)
Z0_POL_G: Q3.1 (G), R23.2, R24.1
Z0_PUMP: R25.1, U1.16 (GPIO12)
Z0_PUMP_D: D12.2 (A), J17.2, Q4.3 (D)
Z0_PUMP_G: Q4.1 (G), R25.2, R26.1
Z0_RELAY: R21.1, U1.14 (GPIO10)
Z0_RELAY_D: D9.2 (A), J14.2, Q2.3 (D)
Z0_RELAY_G: Q2.1 (G), R21.2, R22.1
Z1_COIL_P: D15.1 (K), J20.2, J21.1
Z1_FAN: R37.1, U1.25 (GPIO19)
Z1_FAN_D: D19.2 (A), J25.2, Q9.3 (D)
Z1_FAN_G: Q9.1 (G), R37.2, R38.1
Z1_FLOW: D20.3 (COM), R39.2, R40.1, U1.26 (GPIO20)
Z1_FLOW_IN: J26.3, R39.1
Z1_NTC_H: J7.1, R11.2, R12.1
Z1_NTC_W: J6.1, R9.2, R10.1
Z1_POL: R33.1, U1.22 (GPIO17)
Z1_POL_D: D16.2 (A), D17.2 (A), J22.2, J23.2, Q7.3 (D)
Z1_POL_G: Q7.1 (G), R33.2, R34.1
Z1_PUMP: R35.1, U1.24 (GPIO18)
Z1_PUMP_D: D18.2 (A), J24.2, Q8.3 (D)
Z1_PUMP_G: Q8.1 (G), R35.2, R36.1
Z1_RELAY: R31.1, U1.21 (GPIO16)
Z1_RELAY_D: D15.2 (A), J21.2, Q6.3 (D)
Z1_RELAY_G: Q6.1 (G), R31.2, R32.1

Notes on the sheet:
Modules: Raspberry Pi Pico 2 (control MCU) + ESP32-S3-DevKitC-1 (hub), OPL UART GP0/GP1 <-> GPIO18/GPIO17
12 V input, fuse, TVS, reverse-polarity P-FET, 12->5 V buck (LM2596S-5.0), 5 V ORing, test points
ADS1115 @0x48 (ADDR=GND) on I2C0 GP8/GP9, NTC dividers 3.3 V - 10k 0.1 % - node - NTC - GND
RS-485 to the DPS modules: SP3485 on UART1 GP4/GP5, DE+/RE on GP6
Fail-safe inputs: LEAK GP21, LEVEL GP22 (LOW = good, open wire = HIGH = fault)
Zone 0 drivers (GP10 relay, GP11 polarity, GP12 pump, GP13 fan, GP14 flow) and sensors
Zone 1 drivers (GP16 relay, GP17 polarity, GP18 pump, GP19 fan, GP20 flow) and sensors
Mounting holes
Power flags

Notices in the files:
hardware/pcb/carrier/carrier.kicad_pcb:
CERN-OHL-S-2.0 - hardware/pcb/carrier
hardware/pcb/carrier/carrier.kicad_sch:
Open Bed Climate - CERN-OHL-S-2.0
